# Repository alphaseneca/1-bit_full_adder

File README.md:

# Full Adder

## Overview

A **1-bit Full Adder** is a basic circuit used to add three input bits: two data bits (**A** and **B**) and a carry-in bit (**Cin**).

It produces two outputs:

- **Sum**: The result of the addition.
- **Carry (Cout)**: The carry passed to the next bit in case of multi-bit additions.

This circuit plays an important role in digital electronics and serves as the foundation for larger systems like multi-bit adders used in microprocessors.

## Design and Implementation

### Initial Plan

At first, I followed the typical textbook design, which uses:

- **2 XOR gates**
- **2 AND gates**
- **1 OR gate**

This approach worked, but it required more transistors than I expected. Every gate used multiple transistors, so the total count grew quickly.

### Optimized Approach

To make it simpler, I tried using **only NOR gates**. This reduced the number of components, and I was able to build the adder using just **9 transistors**. It was a good way to explore how small changes can make a big difference in circuit design.

## Truth Table

    Sum: A ⊕ B ⊕ Cin
    Carry (Cout): (A · B) + (Cin · (A ⊕ B))

| **A** | **B** | **Cin** | **Sum** | **Cout** |
| :---: | :---: | :-----: | :-----: | :------: |
|   0   |   0   |    0    |    0    |    0     |
|   0   |   0   |    1    |    1    |    0     |
|   0   |   1   |    0    |    1    |    0     |
|   0   |   1   |    1    |    0    |    1     |
|   1   |   0   |    0    |    1    |    0     |
|   1   |   0   |    1    |    0    |    1     |
|   1   |   1   |    0    |    0    |    1     |
|   1   |   1   |    1    |    1    |    1     |

---

## My Design Journey

I first got the idea for this project in my **Digital Logics** class, where we learned about logic gates and how they are built. I thought it would be fun and helpful to build a real circuit and see how the gates work together. I had already made a schematic of the prototype earlier, but the final version came together during **Workshop 101** by **LAB448** at **Pashchimanchal Campus**.

## PCB

After the success of the prototype, I decided to make a PCB for the adder. This pcb is designed to be used as a module to make the student understand the concept of full adder.

---

## References

- [9 transistor full adder [YouTube]](https://www.youtube.com/watch?v=DtL7BKjrqFo)
- [Fundamental of TTL gates](http://hyperphysics.phy-astr.gsu.edu/hbase/Electronic/trangate.html)

This repository not only tracks the **1-bit Full Adder** but also keeps a record of my progress and future updates. It will serve as a reference for new experiments and improvements.

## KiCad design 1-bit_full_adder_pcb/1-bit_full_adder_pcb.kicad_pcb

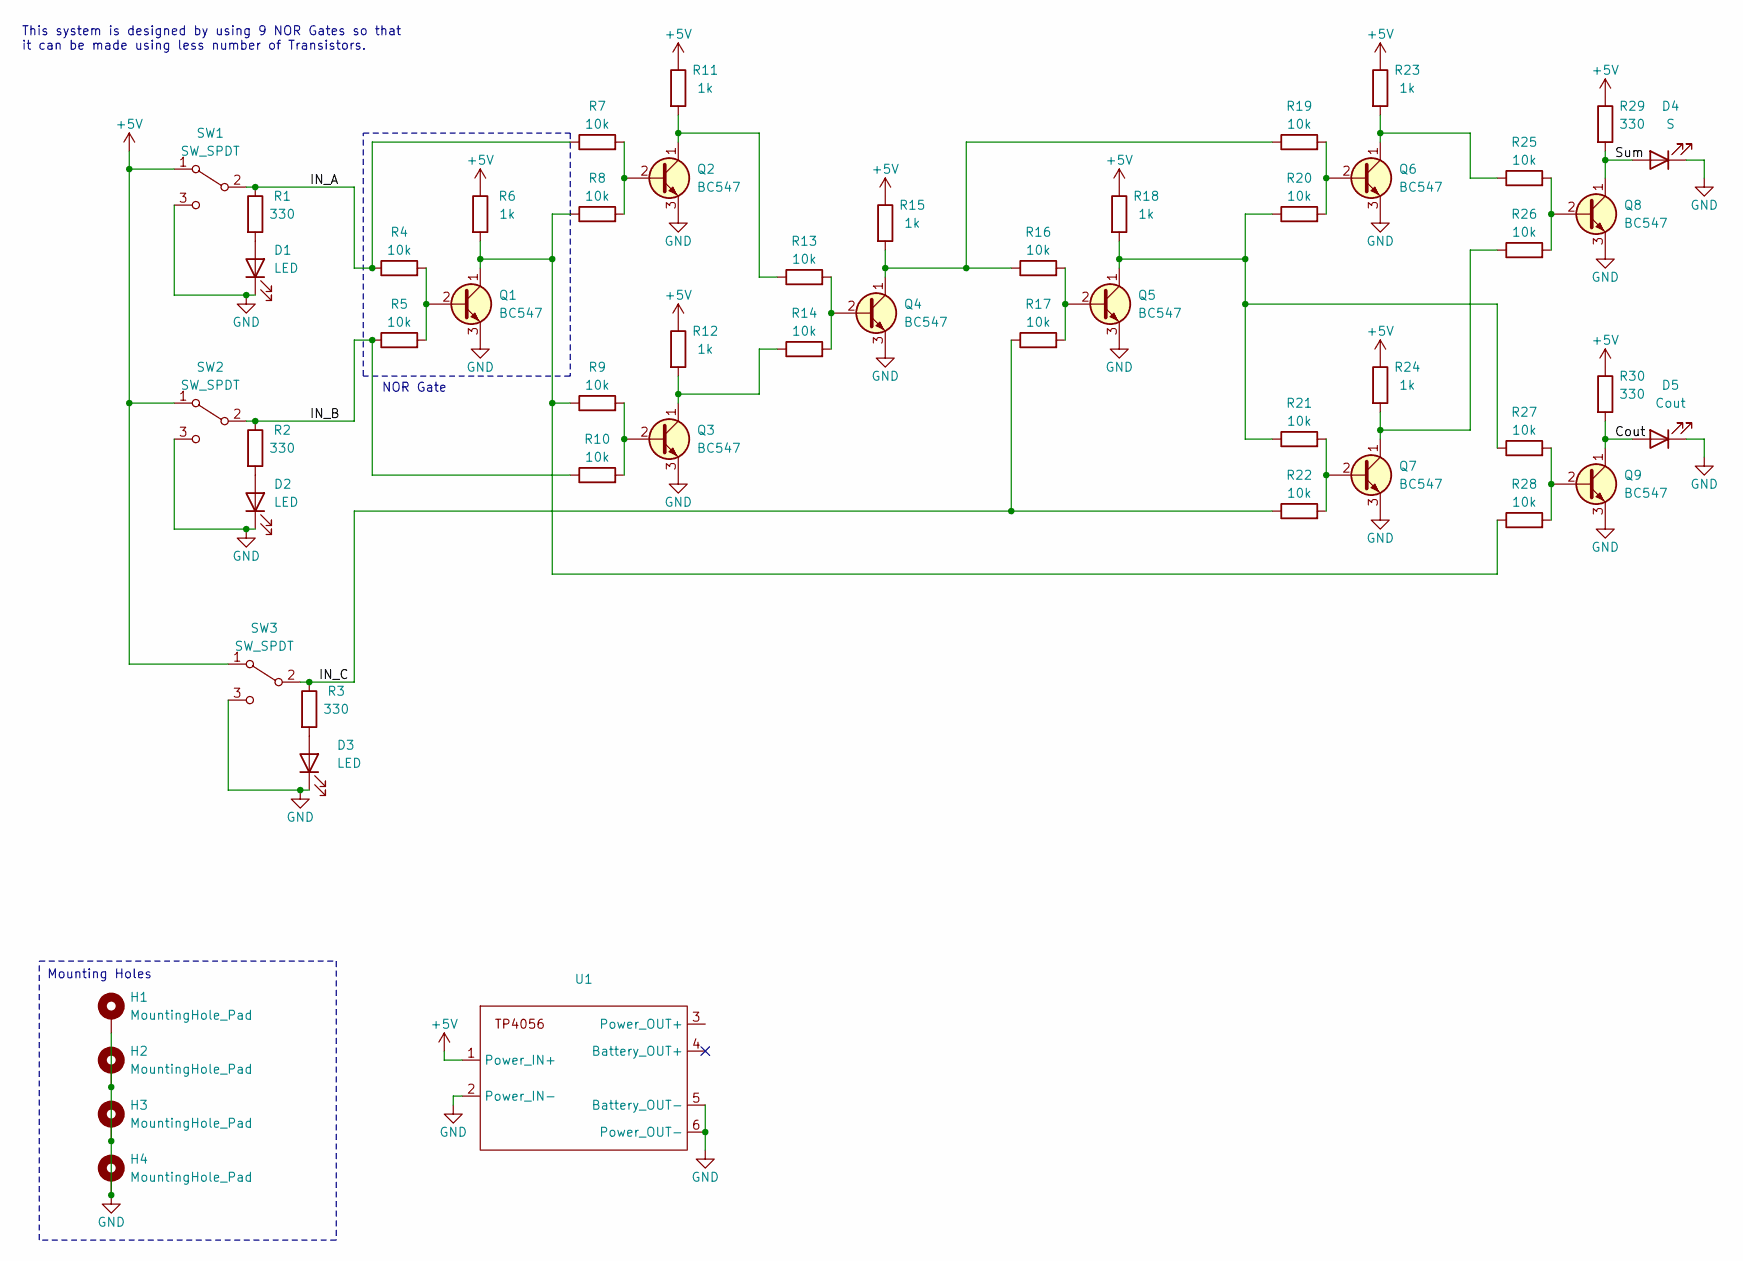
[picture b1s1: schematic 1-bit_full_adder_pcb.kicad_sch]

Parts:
D1, D2, D3: LED; LED_D3.0mm
D4: S; LED_D3.0mm
D5: Cout; LED_D3.0mm
H1, H2, H3, H4: MountingHole_Pad; MountingHole_2.2mm_M2_Pad_TopBottom
Q1, Q2, Q3, Q4, Q5, Q6, Q7, Q8, Q9: BC547; TO-92_Inline_CBE
R1, R2, R3, R29, R30: 330; R_Axial_DIN0207_L6.3mm_D2.5mm_P10.16mm_Horizontal
R4, R5, R7, R8, R9, R10, R13, R14, R16, R17, R19, R20, R21, R22, R25, R26, R27, R28: 10k; R_Axial_DIN0207_L6.3mm_D2.5mm_P10.16mm_Horizontal
R6, R11, R12, R15, R18, R23, R24: 1k; R_Axial_DIN0207_L6.3mm_D2.5mm_P10.16mm_Horizontal
SW1, SW2, SW3: SW_SPDT; SWITCH_S20203
U1: tp4056_module

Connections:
+5V: R6.1, R11.1, R12.1, R15.1, R18.1, R23.1, R24.1, R29.1, R30.1, SW1.1 (A), SW2.1 (A), SW3.1 (A), U1.1 (Power_IN+); also elsewhere on the board
/Cout: D5.2 (A), Q9.1 (C), R30.2
/IN_A: R1.1, R4.1, R7.1, SW1.2 (B); also elsewhere on the board
/IN_B: R2.1, R5.1, R10.1, SW2.2 (B); also elsewhere on the board
/IN_C: R3.1, R17.1, R22.1, SW3.2 (B); also elsewhere on the board
/Sum: D4.2 (A), Q8.1 (C), R29.2
GND: D1.1 (K), D2.1 (K), D3.1 (K), D4.1 (K), D5.1 (K), H1.1, H2.1, H3.1, H4.1, Q1.3 (E), Q2.3 (E), Q3.3 (E), Q4.3 (E), Q5.3 (E), Q6.3 (E), Q7.3 (E), Q8.3 (E), Q9.3 (E), SW1.3 (C), SW2.3 (C), SW3.3 (C), U1.2 (Power_IN-), U1.5 (Battery_OUT-), U1.6 (Power_OUT-); also elsewhere on the board
unnamed: D1.2 (A), R1.2
unnamed: D2.2 (A), R2.2
unnamed: D3.2 (A), R3.2
unnamed: Q1.2 (B), R4.2, R5.2
unnamed: Q1.1 (C), R6.2, R8.1, R9.1, R28.1
unnamed: Q2.2 (B), R7.2, R8.2
unnamed: Q2.1 (C), R11.2, R13.1
unnamed: Q3.2 (B), R9.2, R10.2
unnamed: Q3.1 (C), R12.2, R14.1
unnamed: Q4.2 (B), R13.2, R14.2
unnamed: Q4.1 (C), R15.2, R16.1, R19.1
unnamed: Q5.2 (B), R16.2, R17.2
unnamed: Q5.1 (C), R18.2, R20.1, R21.1, R27.1
unnamed: Q6.2 (B), R19.2, R20.2
unnamed: Q6.1 (C), R23.2, R25.1
unnamed: Q7.2 (B), R21.2, R22.2
unnamed: Q7.1 (C), R24.2, R26.1
unnamed: Q8.2 (B), R25.2, R26.2
unnamed: Q9.2 (B), R27.2, R28.2

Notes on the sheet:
Mounting Holes
NOR Gate
This system is designed by using 9 NOR Gates so that it can be made using less number of Transistors.

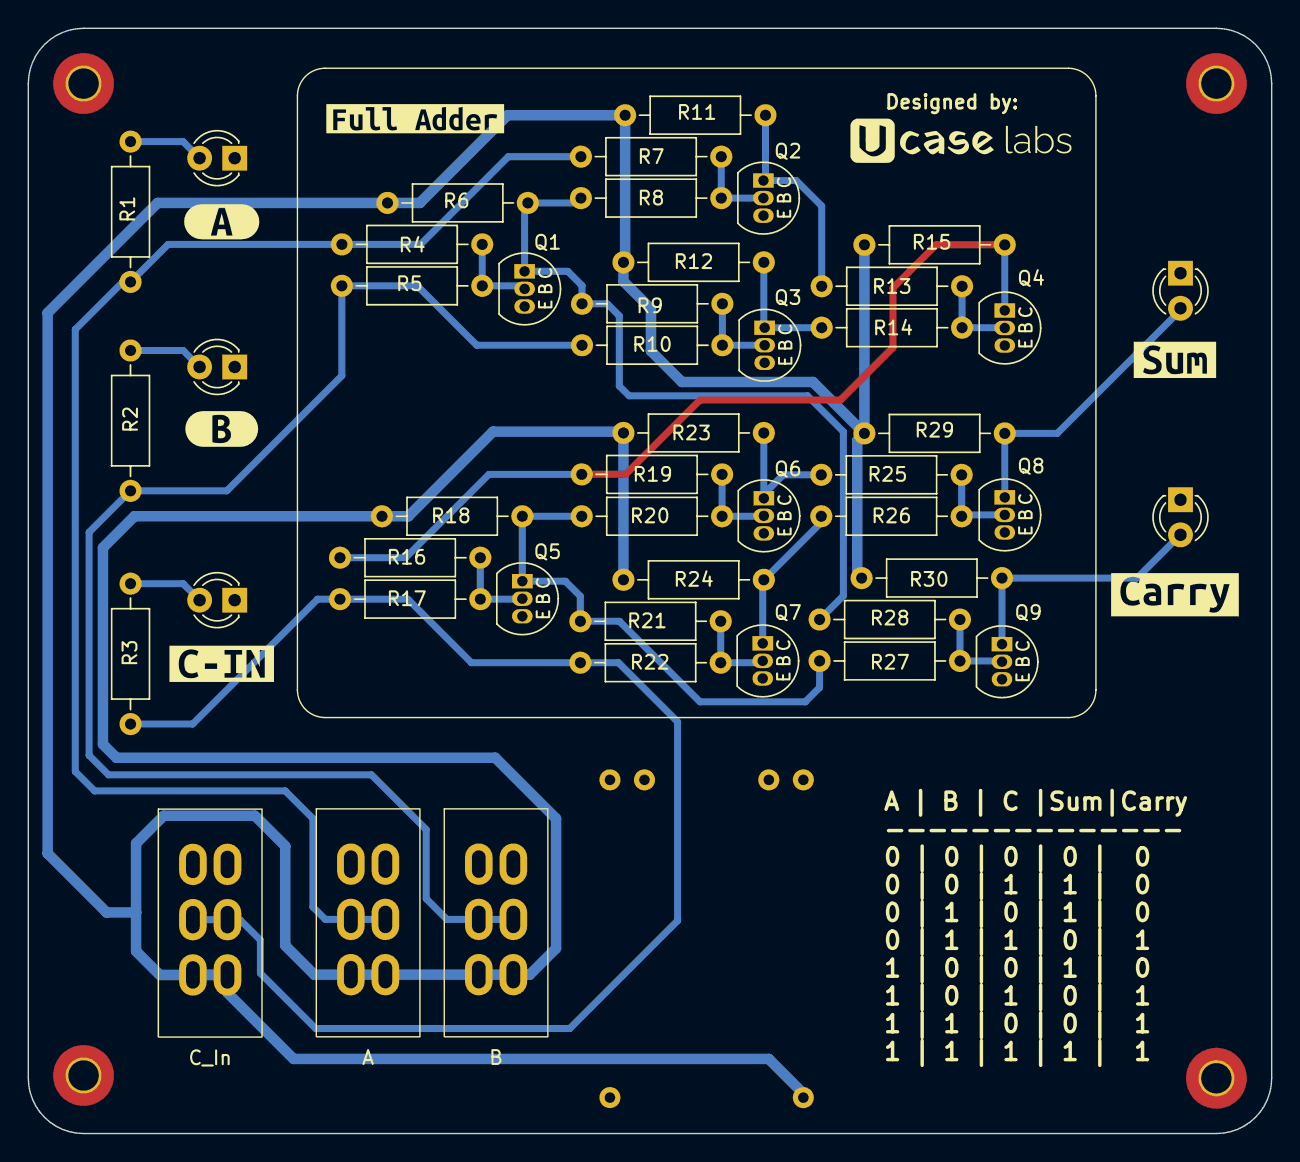
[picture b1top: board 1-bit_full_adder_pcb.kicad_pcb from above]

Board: 2 copper layers, 90.0 x 80.0 mm, 58 parts (1 on the bottom side), 26 nets.

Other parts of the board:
A: SW_SPDT; SWITCH_S20203
B: SW_SPDT; SWITCH_S20203
C_In: SW_SPDT; SWITCH_S20203
kibuzzard-67192DAB: G***; kibuzzard-67192DAB
kibuzzard-67192DB9: G***; kibuzzard-67192DB9
kibuzzard-67192E28: G***; kibuzzard-67192E28
kibuzzard-67192E40: G***; kibuzzard-67192E40
kibuzzard-67192E50: G***; kibuzzard-67192E50
kibuzzard-6724957C: G***; kibuzzard-6724957C

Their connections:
+5V: A.1 (A), B.1 (A), C_In.1 (A); also elsewhere on the board
/IN_A: A.2 (B); also elsewhere on the board
/IN_B: B.2 (B); also elsewhere on the board
/IN_C: C_In.2 (B); also elsewhere on the board
GND: A.3 (C), B.3 (C), C_In.3 (C); also elsewhere on the board

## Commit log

2025-04-24 Updated readme file
2025-04-24 ADD: Images and Files
